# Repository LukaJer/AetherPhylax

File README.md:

# AetherPhylax 

## Tiny Energy Harvesting Environment Monitior 

### Hardware Desctiption:  
- uC: STM32G071
- LoRa Module: RFM95
- power management: BQ25570 (<5.5V)
- I2C 
- 1 GPIO: (PA0 (int0))
- JST ZH 1.5mm connectors
- 1.27mm header for for programming and debugging (SWD+UART)
#### Detailed Description  
It's centered around a STM32G071 microcontroller and uses LoRa for efficient and longish range communication. Currently it sends to a custom Gateway which forwards the data to a MQTT server but the code can be easily adapted to use another LoRa infrastructure like The Things Network. The LoRa Module is a RFM95.  
A 18650 cell (other Li Ion batterys can be used too) is used for power  which is charged  by a TI BQ25570 which harvests energy from a solar panel. The uC can read the solar and battery voltage.  
There is 1 GPIO available (PA0 (int0)) and a I2C bus. The GPIO has a footprins for a pull-up/-down resistor or capacitor and 3V3 and GND connections next to them. JST ZH 1.5mm connectors are used and a 1.5mm pinout is present for programming and debugging (SWD+UART).

### Software Description:
The project is written in Arduino.  
Each Station has it's own name so multiple can be used on a single Gateway. 
The station wakes up in specified Intervalls (2min) and checks if any of the sensor values have changed, if so it sends the data as a JSON to the Gatway. The data is send every 10th wakeup no matter the values as a heartbeat. 
Currently
- Bosch BME280
- Sensiron SHT31
- Lacrosse TX23
- MaXIM DS18B20
- generic simple rain sensor
are implemented an can be enabled by uncommenting code.

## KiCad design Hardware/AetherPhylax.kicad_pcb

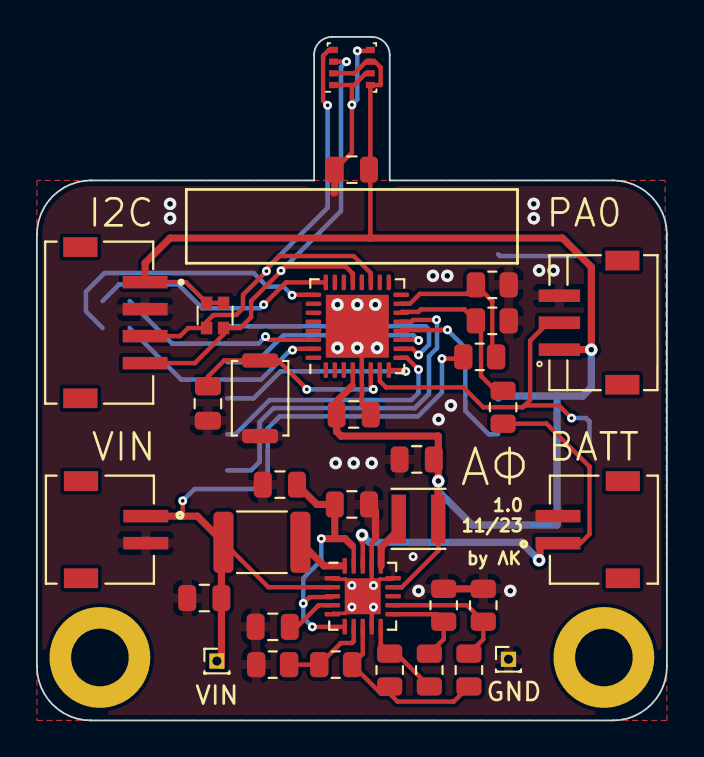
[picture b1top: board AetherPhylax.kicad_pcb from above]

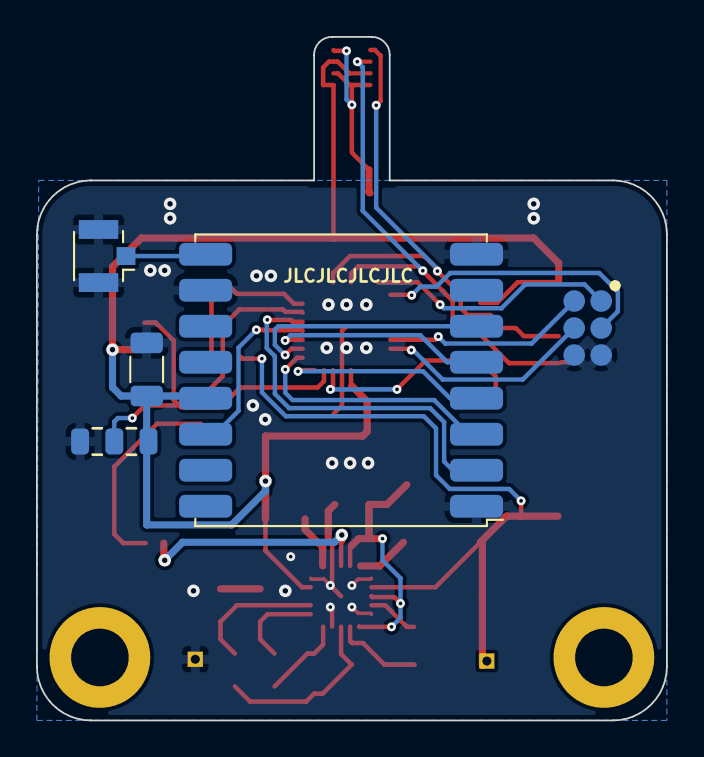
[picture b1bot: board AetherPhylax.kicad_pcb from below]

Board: 2 copper layers, 35.0 x 38.0 mm, 39 parts (5 on the bottom side), 30 nets.

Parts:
ANT1: Conn_Coaxial; U.FL_Hirose_U.FL-R-SMT-1_Vertical
BATT1: Conn_01x02; JST_S2B-ZR-SM4A-TF(LF)(SN)
C1, C2, C3: 0.1uF; C_0805_2012Metric
C4: 1uF; C_1206_3216Metric
CBYP1: 0.01u; C_0805_2012Metric
CIN1: 4.7u; C_0805_2012Metric
COUT1: 22u; C_0805_2012Metric
CREF1: 10n; C_0805_2012Metric
CSTOR1: 4.7u; C_0805_2012Metric
DEBUG1: Conn_02x03_Odd_Even; TestPoint_2x03_1.5mm
H1, H2: M3_Pad; MountingHole_3.2mm_M3_DIN965_Pad
I2C1: Conn_01x04; JST_S4B-ZR-SM4A-TF(LF)(SN)
J1, J2: Conn_01x01_Pin; PinHeader_1x01_P1.00mm_Vertical
JP1: Jumper_3_Open; Jumper_3_0805
L1: 22u; L_1812_4532Metric
L2: 10u; IND_LQH3NPN100MJRL
PA1: Conn_01x03; JST_S3B-ZR-SM4A-TF
R1: 0R; R_0805_2012Metric
R2: 47k; R_0805_2012Metric
R3: DNP; R_0805_2012Metric
R4: 169k; R_0805_2012Metric
RN1: R_Pack02; R_Array_Convex_2x0606
ROK1: 0.3M; R_0805_2012Metric
ROK2: 6.2M; R_0805_2012Metric
ROK3: 3.4M; R_0805_2012Metric
ROUT1: 6.34M; R_0805_2012Metric
ROUT2: 3.57M; R_0805_2012Metric
ROV1: 5.49M; R_0805_2012Metric
ROV2: 4.42M; R_0805_2012Metric
RST1: SW_Push; SW_Push_SPST_NO_Alps_SKRK
U1: QFN-20-1EP_3.5x3.5mm_P0.5mm_EP2x2mm
U2: BME280; Bosch_LGA-8_2.5x2.5mm_P0.65mm_ClockwisePinNumbering
U3: STM32G071KxU; UFQFPN-32-1EP_5x5mm_P0.5mm_EP3.5x3.5mm
U4: RFM95W-868S2; HOPERF_RFM9XW_SMD
VIN1: Conn_01x02; JST_S2B-ZR-SM4A-TF(LF)(SN)

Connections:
+3V3: C1.1, C2.1, C4.1, COUT1.1, I2C1.1, JP1.3 (B), L2.2, PA1.1, RN1.1 (R1.1), RN1.2 (R2.1), U1.14 (VOUT), U2.2 (CSB), U2.6 (VDDIO), U2.8 (VDD), U3.4 (VDD/VDDA), U4.13 (3.3V)
+BATT: BATT1.1, R2.1, U1.18 (VBAT)
/VBAT_OV: ROV1.2, ROV2.1, U1.7 (VBAT_OV)
/VOUT_SET: ROUT1.2, ROUT2.1, U1.12 (VOUT_SET)
/VSTOR: CBYP1.1, CSTOR1.1, U1.3 (VOC_SAMP), U1.6 (VOUT_EN), U1.19 (VSTOR)
ADC_Batt: R2.2, R4.1, U3.14 (PA7)
ADC_Sol: R1.2, R3.1, U3.15 (PB0)
CS: U3.11 (PA4), U4.5 (NSS)
GND: ANT1.2 (Ext), BATT1.2, C1.2, C2.2, C3.2, C4.2, CBYP1.2, CIN1.2, COUT1.2, CREF1.2, CSTOR1.2, DEBUG1.5, DEBUG1.6, I2C1.2, J2.1, JP1.1 (A), PA1.3, R3.2, R4.2, ROK3.2, ROUT2.2, ROV2.2, RST1.2, U1.1 (VSS), U1.5 (~EN), U1.9 (VSS), U1.15 (VSS), U1.17 (VSS), U1.21 (VSS), U2.1 (GND), U2.5 (SDO), U2.7 (GND), U3.5 (VSS/VSSA), U3.33 (VSS/VSSA), U4.1 (GND), U4.8 (GND), U4.10 (GND), VIN1.2
INT: U3.12 (PA5), U4.14 (DIO0)
MISO: U3.13 (PA6), U4.2 (MISO)
MOSI: U3.9 (PA2), U4.3 (MOSI)
unnamed: ANT1.1 (In), U4.9 (ANT)
unnamed: L1.2, U1.20 (LBOOST)
unnamed: L2.1, U1.16 (LBUCK)
unnamed: ROK1.2, ROK2.1, U1.10 (OK_HYST)
unnamed: ROK2.2, ROK3.1, U1.11 (OK_PROG)
unnamed: ROK1.1, ROUT1.1, ROV1.1, U1.8 (VRDIV)
unnamed: CREF1.1, U1.4 (VREF_SAMP)
unnamed: C3.1, RST1.1, U3.6 (~RST/PF2)
PA0: JP1.2 (C), PA1.2, U3.7 (PA0)
RST: U3.10 (PA3), U4.6 (RESET)
RX: DEBUG1.4, U3.31 (PB7)
SCK: U3.8 (PA1), U4.4 (SCK)
SCL: I2C1.3, RN1.3 (R2.2), U2.4 (SCK), U3.19 (PA9)
SDA: I2C1.4, RN1.4 (R1.2), U2.3 (SDI), U3.21 (PA10)
SWCLK: DEBUG1.3, U3.25 (PA14/BOOT0)
SWDIO: DEBUG1.1, U3.24 (PA13)
TX: DEBUG1.2, U3.30 (PB6)
VDD: CIN1.1, J1.1, L1.1, R1.1, U1.2 (VIN_DC), VIN1.1

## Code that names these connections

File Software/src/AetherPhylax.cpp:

#define RH_ENABLE_ENCRYPTION_MODULE
#include <RH_RF95.h>
#include <Arduino.h>
#include <RHEncryptedDriver.h>
#include <Speck.h>
#include <Wire.h>
#include <ArduinoJson.h>
#include <LaCrosse_TX23.h>
#include "STM32LowPower.h"

// General Pin Definitions
#define RFM95_RST PA3
#define RFM95_CS PA4
#define RFM95_INT PA5
#define MISO PA6
#define MOSI PA2
#define SCK PA1
#define I2C_SDA PA10
#define I2C_SCL PA9

#define F_CPU 16000000

// Uncomment used Sensors:
// #define WIND
#define BME280
// #define RMTSENS
// #define SHT31
// #define RAIN

// Radiohead RF95 Driver
RH_RF95 rf95(RFM95_CS, RFM95_INT);			// Instanciate a LoRa driver
Speck myCipher;								// Instanciate a Speck block ciphering
RHEncryptedDriver myDriver(rf95, myCipher); // Instantiate the driver with those two

// Bosch BME280 Definition
#ifdef BME280
#include <Adafruit_Sensor.h>
#include <Adafruit_BME280.h>
#define SEALEVELPRESSURE_HPA (1013.25)
Adafruit_BME280 bme;
float Temp, Hum, Press;
byte BME280init_ok = 0, BME280_ok = 0;
#endif // BME280

// Sensorion SHT31 Definition
#ifdef SHT31
#include "Adafruit_SHT31.h"
Adafruit_SHT31 sht31 = Adafruit_SHT31();
float Temp1, Hum1;
#endif // SHT31

// MaXIM DS18B20 Definition
#ifdef RMTSENS
#define RemoteTempPin PA15
#include <OneWire.h>
#include <DallasTemperature.h>
OneWire oneWire(RemoteTempPin);
DallasTemperature RemoteSensor(&oneWire);
#endif // RMTSENS

// LaCrosse TX23 Definition
#ifdef WIND
#define Wind_Pin PB8
LaCrosse_TX23 anemometer = LaCrosse_TX23(Wind_Pin);
float speed, speed_old;
uint16_t dir, dir_old;
#endif // WIND

// Generic Rain Interrupt Sensor Definition
#ifdef RAIN
#define rainPin PA0 // fixed!!
volatile uint8_t rainPulses = 0;
void rainfct();
#endif // RAIN

float frequency = 868.0;																// LoRa Frequency
unsigned char encryptkey[16] = {1, 2, 3, 4, 5, 6, 7, 8, 9, 10, 11, 12, 13, 14, 15, 16}; // The very secret key
String name = "APhi0";																	// Name of the Weather Station
uint8_t HWMessageLen, nrWakeup = 0;
DynamicJsonDocument payload(512);			   // JSON Definition (might be shortened)
int SendInterval_LP = 600, SendInterval = 120; //  (Low Power) Send Intervall in Seconds
int ValChng = 0;							   // Tracks if values have changed
float VBatt, VSol;

void setup()
{
	// Set UART Pins
	Serial.setRx(PB7);
	Serial.setTx(PB6);
	Serial.begin(9600);

	payload["Name"] = name;
	Serial.println("AetherPhylax Client: " + name);
	delay(100);

	// Set I2C Pins
	Wire.setSDA(I2C_SDA);
	Wire.setSCL(I2C_SCL);
	Wire.begin();

// Sensor Initalisation
#ifdef BME280
	unsigned status;
	status = bme.begin(0x76);
	if (!status)
	{
		Serial.println("Could not find a valid BME280 sensor, check wiring, address, sensor ID!");
		Serial.print("SensorID was: 0x");
		Serial.println(bme.sensorID(), 16);
		Serial.print("        ID of 0xFF probably means a bad address, a BMP 180 or BMP 085\n");
		Serial.print("   ID of 0x56-0x58 represents a BMP 280,\n");
		Serial.print("        ID of 0x60 represents a BME 280.\n");
		Serial.print("        ID of 0x61 represents a BME 680.\n");
				BME280init_ok = 0;
		BME280_ok = 0;
	}
	else
	{
		BME280init_ok = 1;
		BME280_ok = 1;
	}

#endif // BME280

#ifdef SHT31
	if (!sht31.begin(0x44))
	{ // Set to 0x45 for alternate i2c addr
		Serial.println("Couldn't find SHT31");
		while (1)
			delay(1);
	}
#endif // SHT31

#ifdef RMTSENS
	RemoteSensor.begin();
#endif // RMTSENS

	// Set SPI Pins
	SPI.setMISO(MISO);
	SPI.setMOSI(MOSI);
	SPI.setSCLK(SCK);
	delay(10);

	// LoRa Initalisation
	if (!rf95.init())
	{
		Serial.println("LoRa init failed");
		while (1) // Halt Startup if RF95 not found
			delay(1);
	}
	rf95.setFrequency(frequency);
	rf95.setTxPower(13);
	myCipher.setKey(encryptkey, sizeof(encryptkey));

	LowPower.begin();
// Enable Rain Interrupt
#ifdef RAIN
	pinMode(rainPin, INPUT_FLOATING);
	LowPower.attachInterruptWakeup(rainPin, rainfct, RISING, DEEP_SLEEP_MODE);
#endif // RAIN

	Serial.println("Setup completed");
	delay(1000);
}

void loop()
{

	float buffer = 0;

	delay(50);
	Serial.print("Wake-Up Nr: ");
	Serial.println(nrWakeup);
	// Keeping Track of #Wakeups
	nrWakeup++;
	// Data gets send every 10th wake-up independent wether data has changed: Heartbeat
	if (!(nrWakeup % 10))
	{
		ValChng = 1;
		if (!BME280_ok)
			LowPower.shutdown(100); // Restart
	}
	delay(50);

#ifdef RAIN
	Serial.print("Rainpulse: ");
	Serial.println(rainPulses);
#endif

// Read Wind Data
#ifdef WIND
	if (anemometer.read(speed, dir))
	{
		Serial.println("Wind found");
		/* Wind Data gets only sent if speed is greater 0 and
		Speedchange > 0.5 or
		ValChng = 1 or
		Direction Change > 0.5
		*/
		if (abs(speed_old - speed) > 0.5 || ValChng || ((abs(dir_old - dir) > 0.5) && speed > 0))
		{
			ValChng = 1;
			payload["Speed"] = speed;
			speed_old = speed;
			payload["Dir"] = dir * 22.5;
			dir_old = dir;
		}
	}
#endif // WIND

// Read BME280 Data
#ifdef BME280
	if (BME280init_ok)
	{
		if (bme.takeForcedMeasurement())
		{
			BME280_ok = 1;
			/* BEM280 Data gets only sent if
			Temperaturechange > 0.5°C or
			Humiditychange > 5%
			*/
			buffer = bme.readTemperature() / 1.0;
			if (abs(Temp - buffer) > 0.5 || ValChng)
			{
				ValChng = 1;
				payload["Temp"] = buffer;
				Temp = buffer;
			}
			buffer = roundf(bme.readHumidity() * 100) / 100;
			if (abs(Hum - buffer) > 5 || ValChng)
			{
				ValChng = 1;
				payload["Hum"] = buffer;
				Hum = buffer;
			}

			buffer = roundf(bme.readPressure()) / 100;
			if (abs(Press - buffer) > 0.5 || ValChng)
			{
				ValChng = 1;
				payload["Press"] = buffer;
				Press = buffer;
			}
		}
		else
			BME280_ok = 0;
	}
#endif // BME280

// Read SHT 31 Data
#ifdef SHT31
	/* SHT31 Data gets only sent if
	Temperaturechange > 0.5°C or
	Humiditychange > 5%
	*/
	buffer = sht31.readTemperature();
	if (abs(Temp1 - buffer) > 0.5 || ValChng)
	{
		ValChng = 1;
		payload["Temp1"] = buffer;
		Temp1 = buffer;
	}

	buffer = sht31.readHumidity();
	if (abs(Hum1 - buffer) > 5 || ValChng)
	{
		ValChng = 1;
		payload["Hum1"] = buffer;
		Hum1 = buffer;
	}
#endif // SHT31

// Read Remote Sensor Data
#ifdef RMTSENS
	float RemoteTemp(NAN);
	RemoteSensor.requestTemperatures();
	RemoteTemp = RemoteSensor.getTempCByIndex(0);
	if (RemoteTemp != -127)
	{
		payload["RmtTmp"] = RemoteTemp;
	}
#endif // RMTSENS

#ifdef RAIN
	payload["RainC"] = rainPulses;
#endif // RAIN

	if (!ValChng)
	{
		// Don't send anything if no new Data or not a 10th wakeup
		Serial.println("No new Data, back to zzzz");
		delay(50);

		LowPower.deepSleep(SendInterval * 1000);
	}
	else
	{
#ifdef RAIN
		rainPulses = 0; // Reset RainPulses
#endif
		// Read Battery and Solar Voltages (8bit)
		VBatt = analogRead(PA7) * 4.3 / 1024;
		VSol = analogRead(PB0) * 10.9 / 1024;
		payload["VBatt"] = trunc(VBatt * 100) / 100;
		if (floor(VSol) > 0)
		{
			payload["VSol"] = trunc(VSol * 100) / 100;
		}

		size_t len = 32;
		char message[256]; // SerializedJSON, replace with len?
		len = payload.memoryUsage();
		Serial.println(len);
		serializeJson(payload, message); // Create String (Char Array) from JSON
		uint8_t data[len + 1];			 // RFM95 input

		for (uint8_t i = 0; i <= len; i++) // Copy and Typecast Data from JSONString to uint8_t Array
		{
			data[i] = (uint8_t)message[i];
		}
		data[len + 1] = '\0';
		myDriver.send(data,  (uint8_t)sizeof(data)); // Send out ID + Sensor data to LoRa gateway
		Serial.print("Sent: ");
		delay(50);
		Serial.println((char *)&data);
		delay(50);
		rf95.sleep(); // Put RF95 to sleep
		ValChng = 0;
		delay(100);
		// Check if Battery is above 3V, if not use LowPower Intervall for Wakups, current not used!
		if (VBatt > 3.0)
			LowPower.deepSleep(SendInterval * 1000);
		else
		{
			LowPower.deepSleep(SendInterval_LP * 1000);
			ValChng = 1;
		}
	}
}

/*
Rain Interrupt triggers this function
Increment Number of Rain Pulses an go back to Sleep
*/
#ifdef RAIN
void rainfct()
{
	rainPulses++;
	delay(50);
	LowPower.deepSleep();
}
#endif // RAIN

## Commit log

2023-12-09 init
2023-12-19 switch to 4Layer Board, fixed I2C Addr
